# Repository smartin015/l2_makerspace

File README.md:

# Level 2 Makerspace

http://l2making.com/

## Overview

This repository contains design docs, software tools, work tracking, and other digital assets to support a Level 2 Makerspace.

See [docs/design.md](https://github.com/smartin015/l2_makerspace/blob/master/docs/design.md) for more detail on the overall mission and planning.

## History & Current State

This is a passion project which started in late 2019 as a chance to collect several technologies and skills which were fun to learn
and had the potential for really interesting applications in making.

Through 2020, my focus has been on prototyping and proving various concepts, including:

* Templates & basic protocols & frameworks (e.g. ROS2, ./infra/base messages & docker container processes)
* Integrations (e.g. Todoist for creating projects, Docker for launching sequences)
* Early hardware proofs of concept (simulation with Webots and publishing compressed point cloud data from Realsense D435 cameras)
* Visualization (particularly in VR, see ./infra/vr/client)
* Networking (e.g. routing between internal ROS network and external VR/app server)

## Roadmap

* See http://app.l2making.com/#project/TODO

## Support

This software is provided as-is with no guarantee of support. 

However, contributions are welcome - please reach out if you're interested
in helping with development.

### Lessons Learned

The following is a collection of details which were learned over hours of frustration. Please read through these if you're stuck on something, and
add new lessons learned.

* ROS2 uses DDS as a backing networking protocol - and it [has issues](https://answers.ros.org/question/296828/ros2-connectivity-across-docker-containers-via-host-driver/) when your run docker containers with the "host" network mode. For simplicity, always use `network_mode: bridge` when setting up docker nodes via docker-compose.
* Docker support for GPU acceleration is device-specific: http://wiki.ros.org/docker/Tutorials/Hardware%20Acceleration#Intel
* A ROS2 subscriber can receive a topic message only if its QOS profile is compatible with the QOS profile of the publisher - [src](https://answers.ros.org/question/304946/ros2-retrieving-qos-settings-for-a-topic/). Nothing tells you this; the messages just aren't received.
* The default docker "bridge" network doesn't allow lookups by container name, only by IP address - must use a user-defined container for name resolution
* ROS message transport (Fast RTPS) breaks if the same PID and IP address are used more than once (https://github.com/ros2/rmw_fastrtps/issues/349)
* If long-running nodes exit with error (137), it's an OOM. `docker ps -a` to find termination time, then `less /var/log/kern.log` and go to the time of death to correlate. 
* ROS nodes don't by default allow you to make nested async calls (e.g. publish from a subscriber callback). A `ReentrantCallbackGroup` must be used (see [vr node](https://github.com/smartin015/l2_makerspace/blob/master/infra/ros/vr/node.py) for an example that also supports service call deadlines).
* Webots ros integration requires the following environment variables to run (as well as sourcing the ROS setup.bash file):
  *  `export LD_LIBRARY_PATH="$LD_LIBRARY_PATH:$WEBOTS_HOME/lib/controller"`
  *  `export PYTHONPATH="$PYTHONPATH:$WEBOTS_HOME/lib/controller/python36"`
  *  `export WEBOTS_HOME=/usr/local/webots`
* As of 2020Q2, Webots doesn't export debian packages for ROS2 Eloquent. If using Crystal, the examples need to be modified to remove QoS settings on publisher definitions:
  *  `/opt/ros/crystal/lib/python3.6/site-packages/webots_ros2_examples/example_controller.py`
  *  `vim /opt/ros/crystal/lib/python3.6/site-packages/webots_ros2_core/webots_node.py`
* You can build webots from source for eloquent; this is probably easier.
* Webots ROS2 Node class has a timer that calls a `timer_callback` callback - accidentally overriding this causes the controller to halt. There's also naming collisions in rclp if you name something "Sequence"
* Sometimes docker-compose takes a looong time to start, with no console output. This was because there was low entropy on the server in order to open a secure connection (see [here](https://github.com/docker/compose/issues/6552))
* Streaming data from Webots requires setting IPC to "host" mode on the docker container; otherwise it exits with a "code 245"
* Ubuntu hides raspi install images for older versions (e.g. 18.04 LTS). You can find them [here](http://cdimage.ubuntu.com/releases/bionic/release/) - but raspbian is the most compatible for running e.g. D435 cameras.
* There's a *ton* of manual effort in setting up a realsense camera on raspi.
  * If you get frame drops, try updating the firmware on the camera. There's some "uvcvideo" kernel module patching stuff that didn't actually work, but could also be helpful. [details](https://eleccelerator.com/wiki/index.php?title=Raspbian_Buster_ROS_RealSense)
* Godot uses `scons` for development. You have to build the binary, then the export templates separately (see [here](https://docs.godotengine.org/en/3.0/development/compiling/compiling_for_x11.html) for linux binary, and [here](https://docs.godotengine.org/en/latest/development/compiling/compiling_for_android.html#building-the-export-templates) for android export templates)
* Super useful librealsense docs around camera intrinsics and projection: [link](https://github.com/IntelRealSense/librealsense/wiki/Projection-in-RealSense-SDK-2.0#intrinsic-camera-parameters)
  * Remember to build with android\_arch=armv7 or else the project will fail to export.
* Can generate space skyboxes with [link](http://wwwtyro.github.io/space-3d), but have to convert (see [link](https://www.reddit.com/r/godot/comments/baw27a/how_to_use_spacescape_skybox_in_godot/))
* Using the Godot OVR toolkit, 2D panels (i.e. most tools in L2 VR) are rendered with the viewport size matching the device resolution. This means tools can have different sizes if they're rendered on different devices (or if you resize the window). Setting display resolution to 2880x1600 makes them match.
* Along with executables, ros2 packages export "components" which can be composeable into nodes. this allows interprocess communciation and other goodies, but is hard to discover. `ros2 component types` (note: not `ros2 components list`) shows which components can be composed.
* Set `"insecure-registries":["<hostname>:5000"]` in /etc/docker/daemon.json and `sudo service docker restart` to allow non-https use of local registry

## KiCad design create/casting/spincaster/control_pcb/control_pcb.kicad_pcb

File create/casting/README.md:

# Casting and Smithing Automation

## Purpose

Automate the casting of metals/resins and "forging" of ductile materials.

## Ideas

TODO

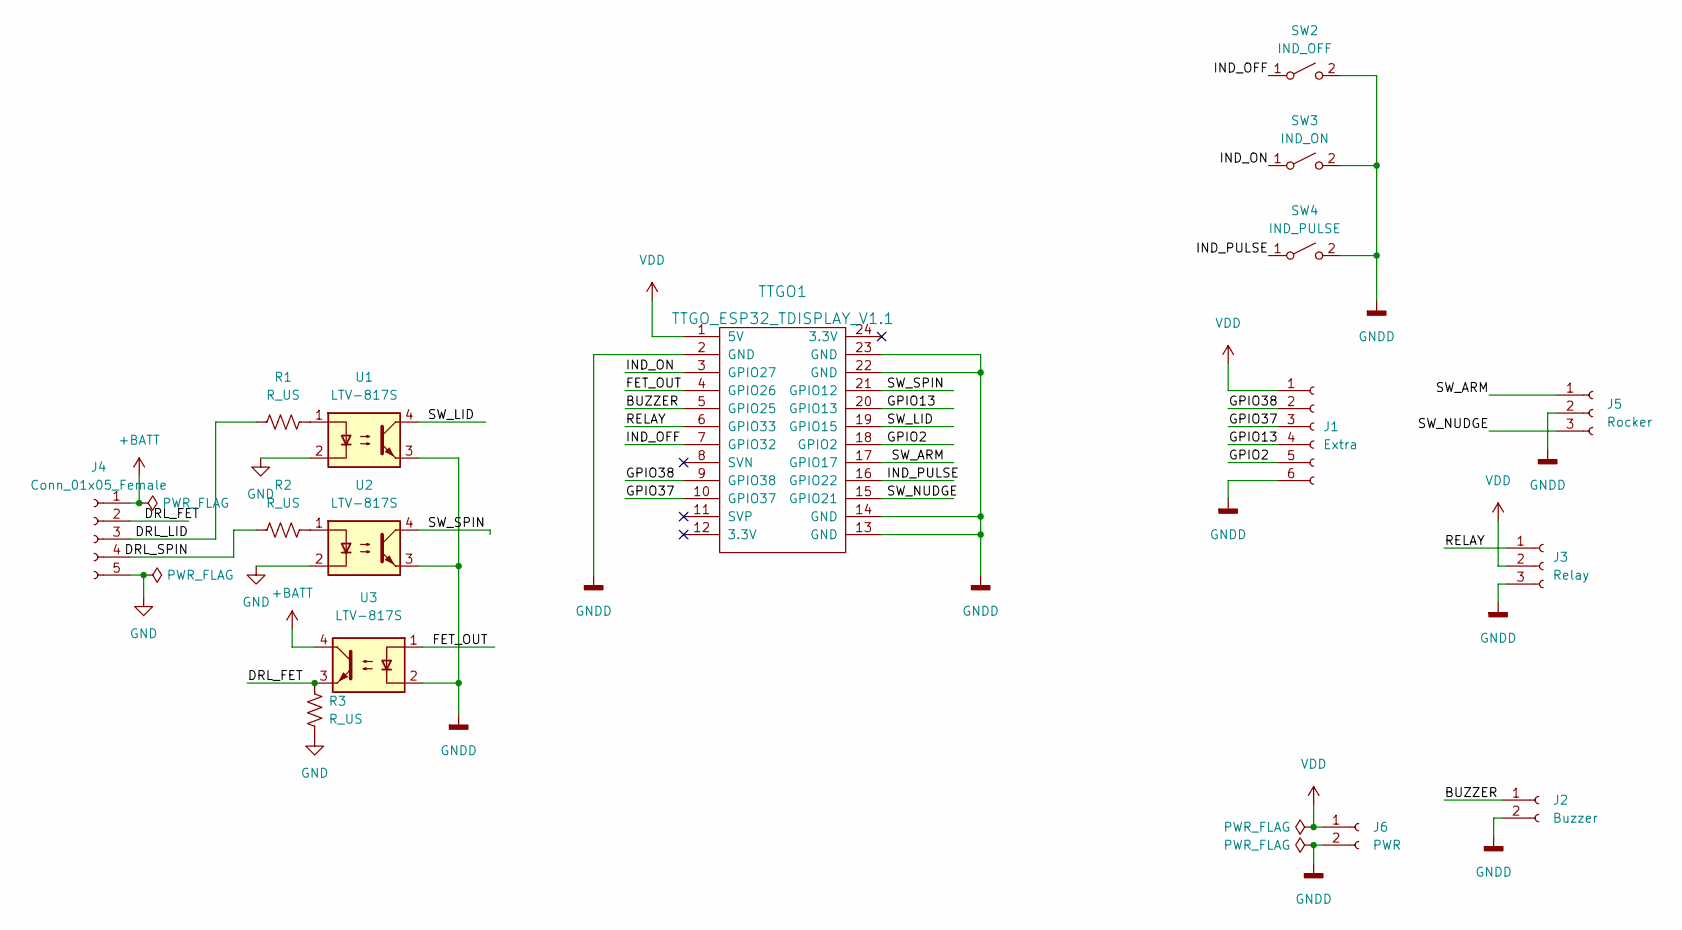
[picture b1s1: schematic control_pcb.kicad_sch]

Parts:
J1: Extra; PinHeader_1x06_P2.54mm_Vertical
J2: Buzzer; JST_PH_B2B-PH-K_1x02_P2.00mm_Vertical
J3: Relay; JST_PH_B3B-PH-K_1x03_P2.00mm_Vertical
J4: Conn_01x05_Female; Molex_KK-254_AE-6410-05A_1x05_P2.54mm_Vertical
J5: Rocker; JST_PH_B3B-PH-K_1x03_P2.00mm_Vertical
J6: PWR; JST_PH_B2B-PH-K_1x02_P2.00mm_Vertical
R1, R2, R3: R_US; R_0805_2012Metric
SW2: IND_OFF; SW_PUSH_6mm_H5mm
SW3: IND_ON; SW_PUSH_6mm_H5mm
SW4: IND_PULSE; SW_PUSH_6mm_H5mm
TTGO1: TTGO_ESP32_TDISPLAY_V1.1; TTGO_ESP32_TDisplay_v1.1
U1, U2, U3: LTV-817S; SMDIP-4_W9.53mm

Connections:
+BATT: J4.1, U3.4
/BUZZER: J2.1, TTGO1.5 (GPIO25)
/DRL_FET: J4.2, R3.1, U3.3
/DRL_LID: J4.3, R1.1
/DRL_SPIN: J4.4, R2.1
/FET_OUT: TTGO1.4 (GPIO26), U3.1
/GPIO2: J1.5, TTGO1.18 (GPIO2)
/GPIO13: J1.4, TTGO1.20 (GPIO13)
/GPIO37: J1.3, TTGO1.10 (GPIO37)
/GPIO38: J1.2, TTGO1.9 (GPIO38)
/IND_OFF: SW2.1 (A), TTGO1.7 (GPIO32)
/IND_ON: SW3.1 (A), TTGO1.3 (GPIO27)
/IND_PULSE: SW4.1 (A), TTGO1.16 (GPIO22)
/RELAY: J3.1, TTGO1.6 (GPIO33)
/SW_ARM: J5.1, TTGO1.17 (GPIO17)
/SW_LID: TTGO1.19 (GPIO15), U1.4
/SW_NUDGE: J5.3, TTGO1.15 (GPIO21)
/SW_SPIN: TTGO1.21 (GPIO12), U2.4
GND: J4.5, R3.2, U1.2, U2.2
GNDD: J1.6, J2.2, J3.3, J5.2, J6.2, SW2.2 (B), SW3.2 (B), SW4.2 (B), TTGO1.2 (GND), TTGO1.13 (GND), TTGO1.14 (GND), TTGO1.22 (GND), TTGO1.23 (GND), U1.3, U2.3, U3.2
unnamed: R1.2, U1.1
unnamed: R2.2, U2.1
VDD: J1.1, J3.2, J6.1, TTGO1.1 (5V)

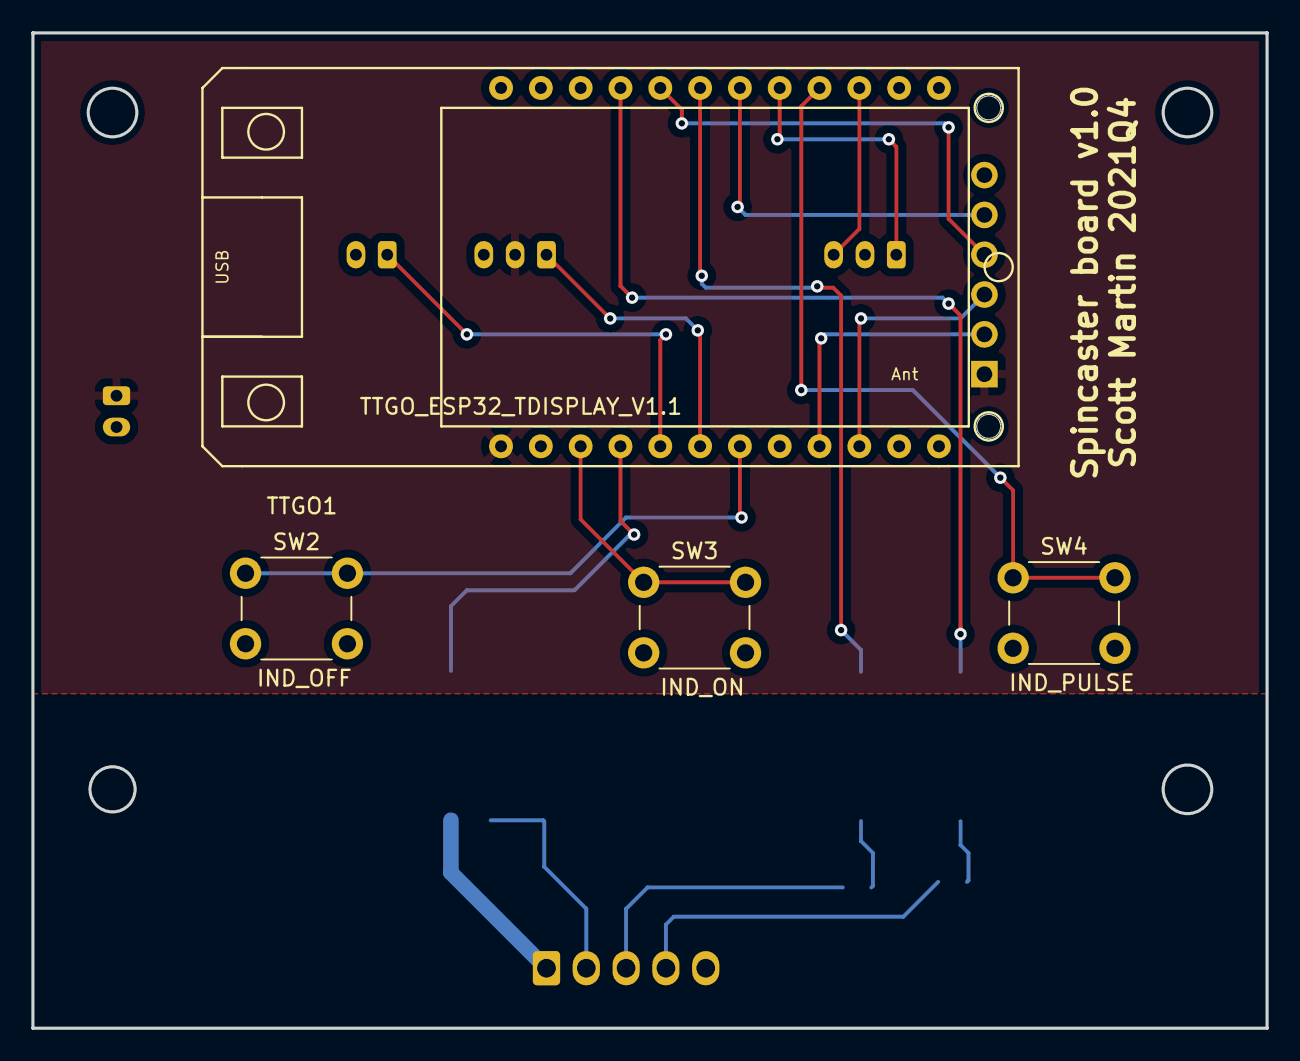
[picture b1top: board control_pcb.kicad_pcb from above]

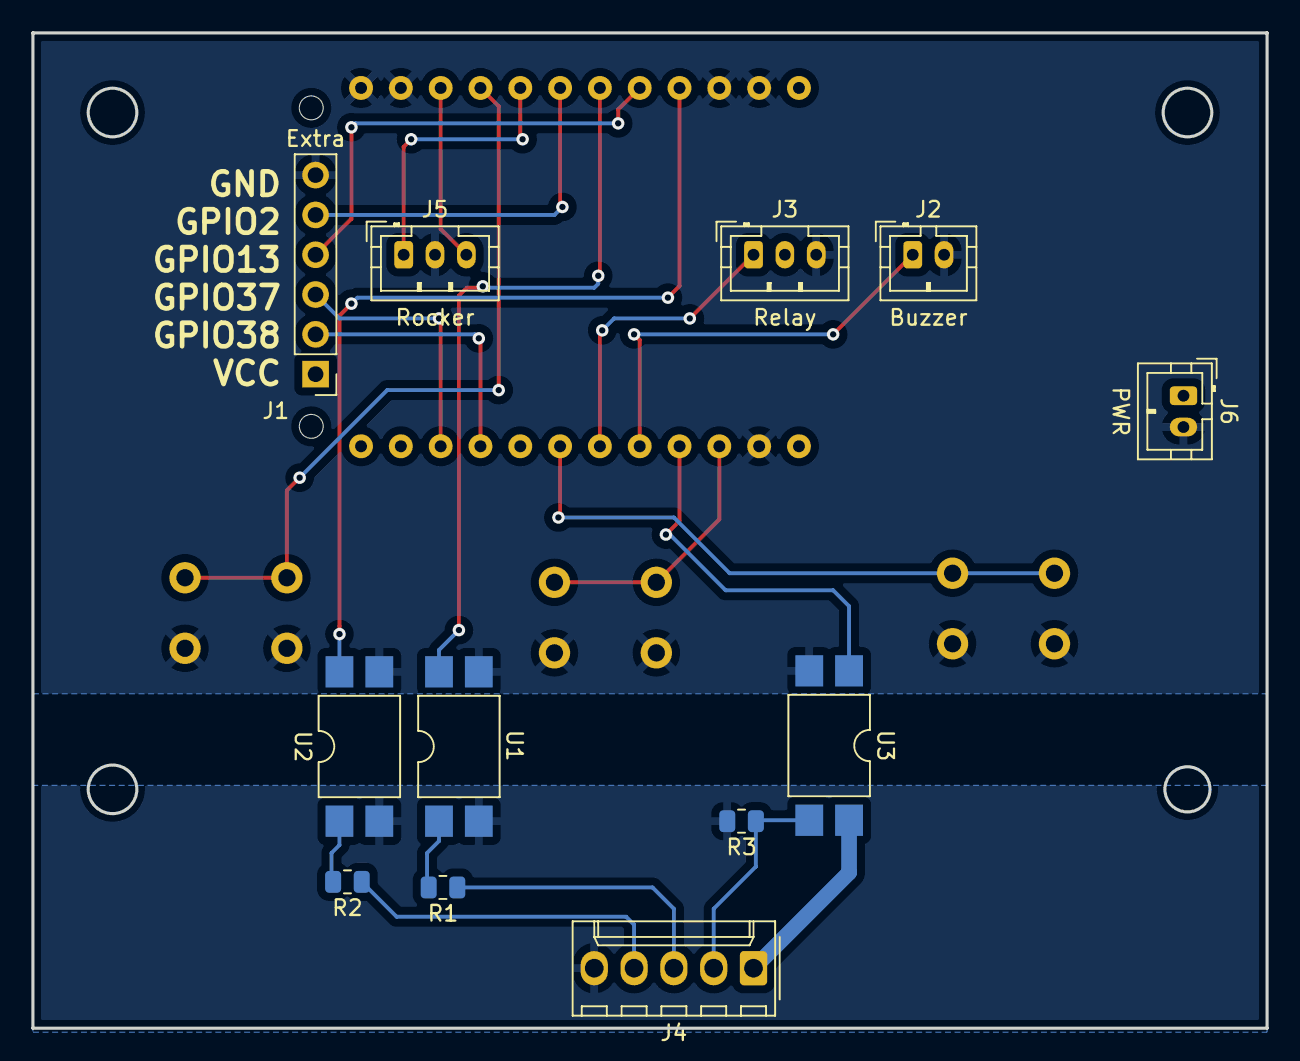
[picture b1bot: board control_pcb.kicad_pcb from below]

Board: 2 copper layers, 78.7 x 63.5 mm, 16 parts (12 on the bottom side), 23 nets.

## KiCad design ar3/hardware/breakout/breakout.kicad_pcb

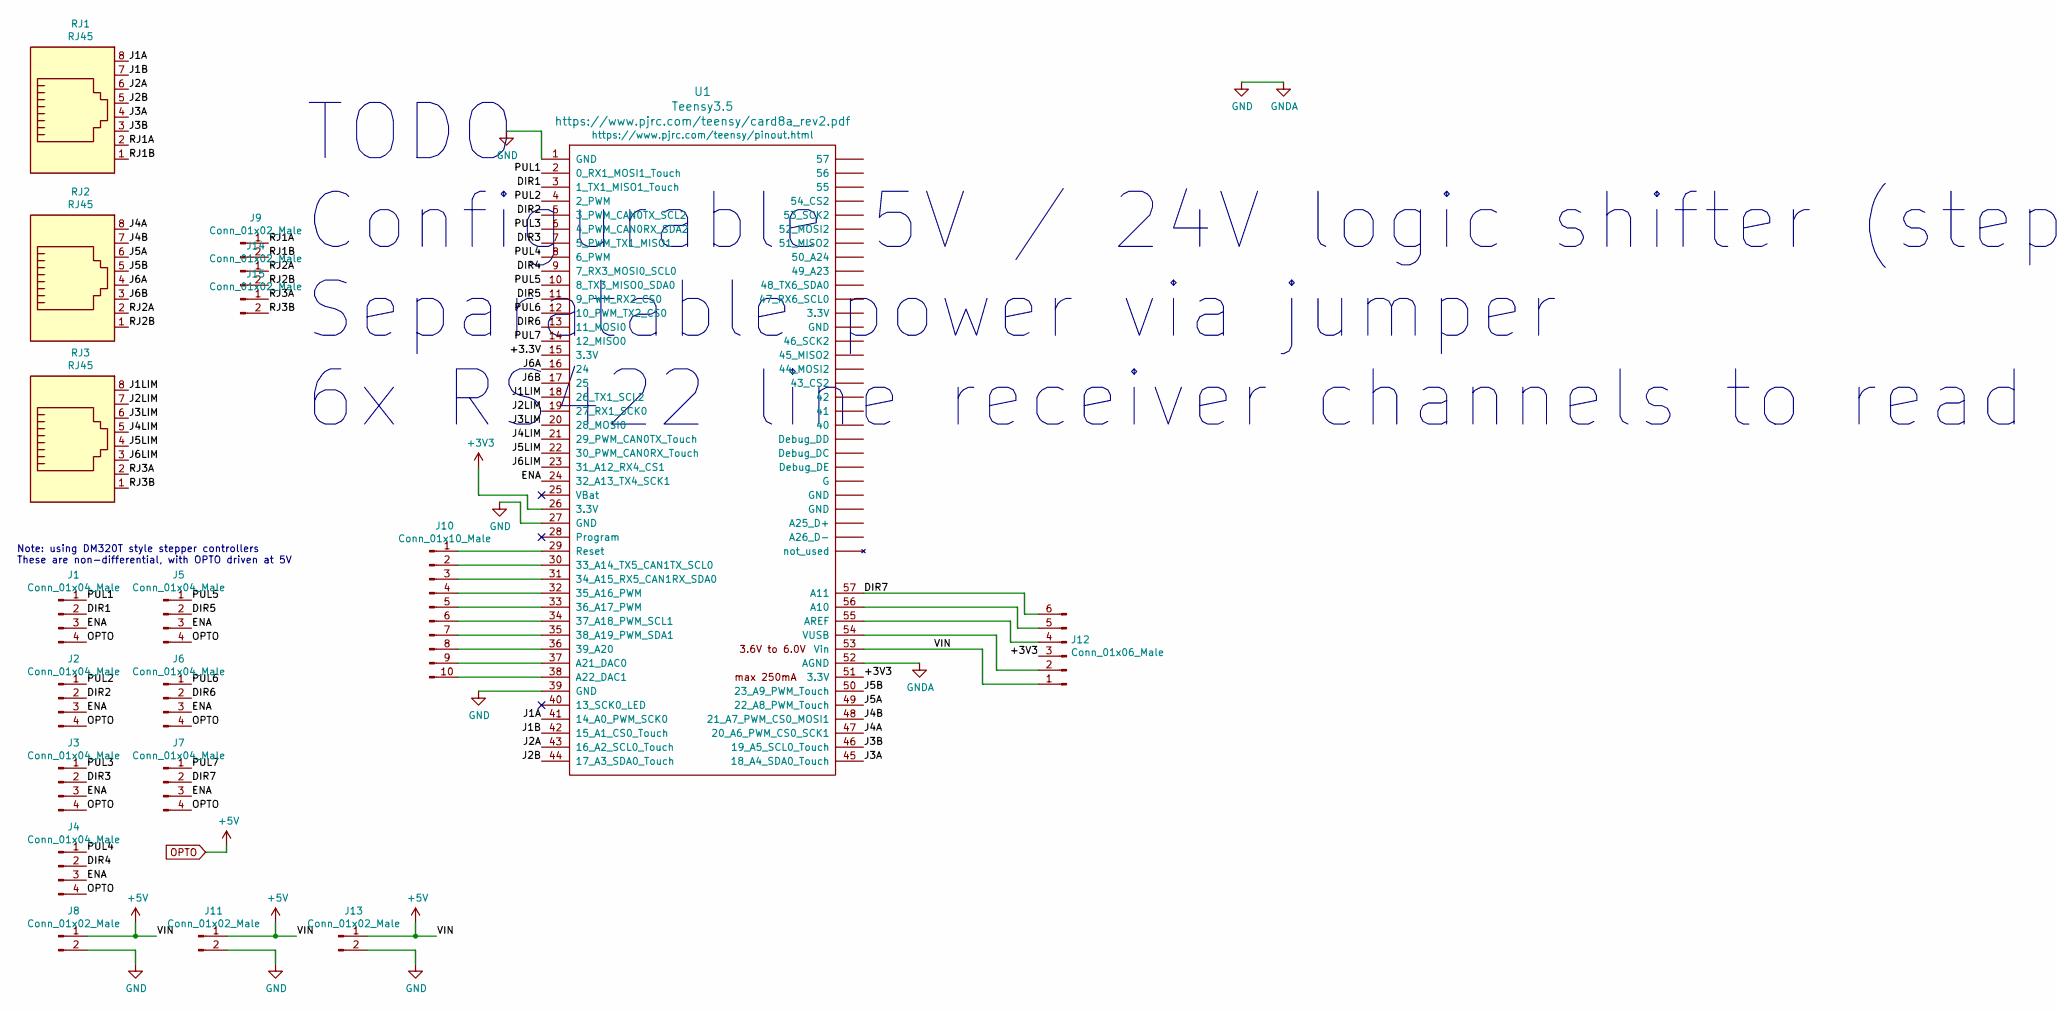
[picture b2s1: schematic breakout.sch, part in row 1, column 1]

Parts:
J1, J2, J3, J4, J5, J6, J7: Conn_01x04_Male; JST_PH_B4B-PH-K_1x04_P2.00mm_Vertical
J8, J9, J11, J13, J14, J15: Conn_01x02_Male; PinHeader_1x02_P2.54mm_Vertical
J10: Conn_01x10_Male; PinHeader_1x10_P2.54mm_Vertical
J12: Conn_01x06_Male; PinHeader_1x06_P2.54mm_Vertical
RJ1, RJ2, RJ3: RJ45; RJ45_Amphenol_54602-x08_Horizontal
U1: Teensy3.5; Teensy35_36

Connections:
+3V3: J12.3, U1.26 (3.3V), U1.51 (3.3V)
/DIR1: J1.2, U1.3 (1_TX1_MISO1_Touch)
/DIR2: J2.2, U1.5 (3_PWM_CAN0TX_SCL2)
/DIR3: J3.2, U1.7 (5_PWM_TX1_MISO1)
/DIR4: J4.2, U1.9 (7_RX3_MOSI0_SCL0)
/DIR5: J5.2, U1.11 (9_PWM_RX2_CS0)
/DIR6: J6.2, U1.13 (11_MOSI0)
/DIR7: J7.2, J12.6, U1.57 (A11)
/ENA: J1.3, J2.3, J3.3, J4.3, J5.3, J6.3, J7.3, U1.24 (32_A13_TX4_SCK1)
/J1A: RJ1.8, U1.41 (14_A0_PWM_SCK0)
/J1B: RJ1.7, U1.42 (15_A1_CS0_Touch)
/J1LIM: RJ3.8, U1.18 (26_TX1_SCL2)
/J2A: RJ1.6, U1.43 (16_A2_SCL0_Touch)
/J2B: RJ1.5, U1.44 (17_A3_SDA0_Touch)
/J2LIM: RJ3.7, U1.19 (27_RX1_SCK0)
/J3A: RJ1.4, U1.45 (18_A4_SDA0_Touch)
/J3B: RJ1.3, U1.46 (19_A5_SCL0_Touch)
/J3LIM: RJ3.6, U1.20 (28_MOSI0)
/J4A: RJ2.8, U1.47 (20_A6_PWM_CS0_SCK1)
/J4B: RJ2.7, U1.48 (21_A7_PWM_CS0_MOSI1)
/J4LIM: RJ3.5, U1.21 (29_PWM_CAN0TX_Touch)
/J5A: RJ2.6, U1.49 (22_A8_PWM_Touch)
/J5B: RJ2.5, U1.50 (23_A9_PWM_Touch)
/J5LIM: RJ3.4, U1.22 (30_PWM_CAN0RX_Touch)
/J6A: RJ2.4, U1.16 (24)
/J6B: RJ2.3, U1.17 (25)
/J6LIM: RJ3.3, U1.23 (31_A12_RX4_CS1)
/PUL1: J1.1, U1.2 (0_RX1_MOSI1_Touch)
/PUL2: J2.1, U1.4 (2_PWM)
/PUL3: J3.1, U1.6 (4_PWM_CAN0RX_SDA2)
/PUL4: J4.1, U1.8 (6_PWM)
/PUL5: J5.1, U1.10 (8_TX3_MISO0_SDA0)
/PUL6: J6.1, U1.12 (10_PWM_TX2_CS0)
/PUL7: J7.1, U1.14 (12_MISO0)
/RJ1A: J9.1, RJ1.2
/RJ1B: J9.2, RJ1.1
/RJ2A: J14.1, RJ2.2
/RJ2B: J14.2, RJ2.1
/RJ3A: J15.1, RJ3.2
/RJ3B: J15.2, RJ3.1
GND: J8.2, J11.2, J13.2, U1.1 (GND), U1.27 (GND), U1.39 (GND), U1.52 (AGND)
unnamed: J10.1, U1.29 (Reset)
unnamed: J10.2, U1.30 (33_A14_TX5_CAN1TX_SCL0)
unnamed: J10.3, U1.31 (34_A15_RX5_CAN1RX_SDA0)
unnamed: J10.4, U1.32 (35_A16_PWM)
unnamed: J10.5, U1.33 (36_A17_PWM)
unnamed: J10.6, U1.34 (37_A18_PWM_SCL1)
unnamed: J10.7, U1.35 (38_A19_PWM_SDA1)
unnamed: J10.8, U1.36 (39_A20)
unnamed: J10.9, U1.37 (A21_DAC0)
unnamed: J10.10, U1.38 (A22_DAC1)
unnamed: J12.2, U1.54 (VUSB)
unnamed: J12.4, U1.55 (AREF)
unnamed: J12.5, U1.56 (A10)
OPTO: J1.4, J2.4, J3.4, J4.4, J5.4, J6.4, J7.4, J8.1, J11.1, J12.1, J13.1, U1.53 (Vin)

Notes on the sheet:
Note: using DM320T style stepper controllers These are non-differential, with OPTO driven at 5V
TODO Configurable 5V / 24V logic shifter (stepper drivers) Separatable power via jumper 6x RS422 line receiver channels to read encoders w/ differential signal

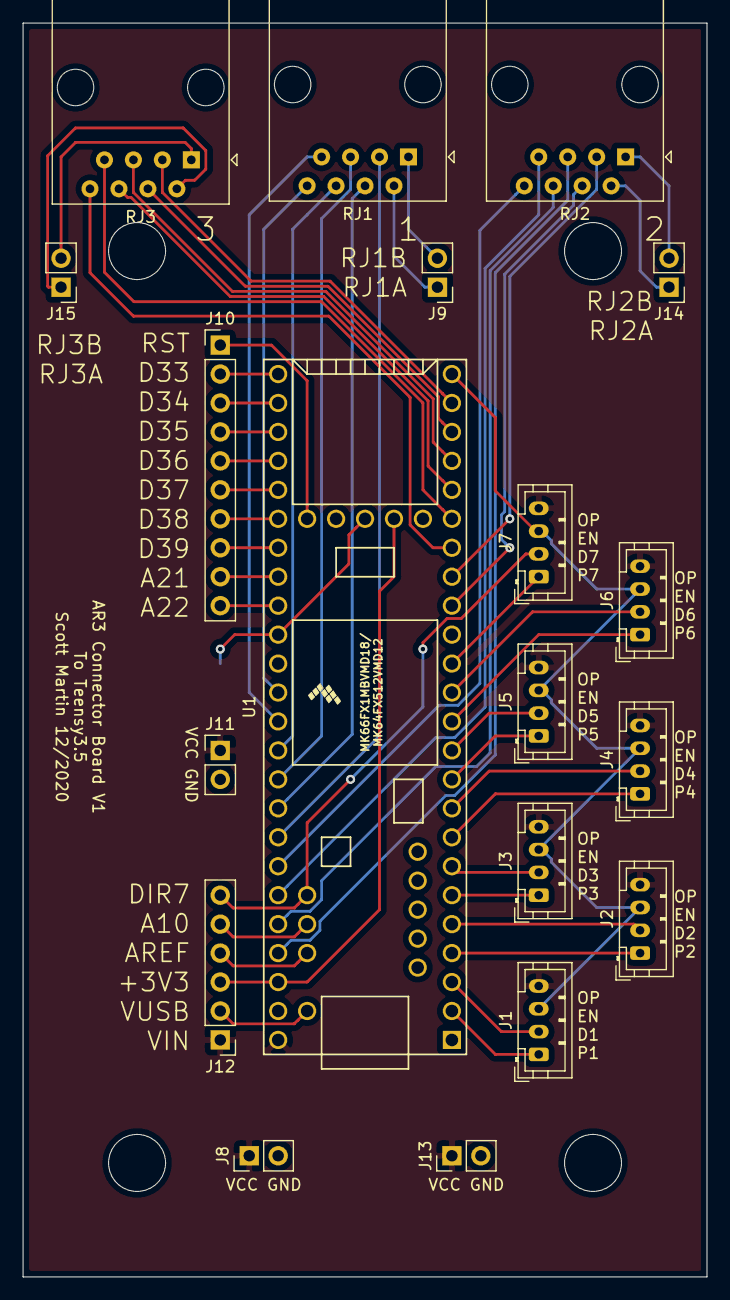
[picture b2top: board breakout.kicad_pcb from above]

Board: 2 copper layers, 60.0 x 110.0 mm, 19 parts (0 on the bottom side), 55 nets.

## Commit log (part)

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2019-12-31 add editor settings
2019-12-31 Add example icon images
2020-01-02 add sketchup file
2020-01-10 Add godot unit testing capability
2020-01-13 First working version of multiplayer, plus keyboard/mouse failover when not using VR
2020-01-13 Add example project message, make storage persist in a file and combine postgres db connection w/ ros2 node
2020-01-14 Moved readme -> docs/design.md, created new top level readme
2020-01-15 Add a starter "bootstrap" doc
2020-01-16 Added some side stuff, fixed cloud deploy & vr server
2020-01-16 Create infra folder and move stuff there
2020-01-16 rm docker.md
2020-01-16 Further refactoring / rearranging
2020-01-17 Added skeleton for todoist tasks ros node
2020-01-19 Add initial example chrome extension
2020-01-22 Continued development on RVL for godot
2020-01-24 Fixed ros talker/listener console flush problem
2020-01-24 Add crappy ros message to typescript interface generator
2020-01-24 Comment out debug text
2020-01-25 Comment out player echo code
2020-01-25 fix apk
2020-01-26 Fixed keyboard navigation and mouselook
2020-01-26 Allowed making cubes with 'g' keyboard press, networked and persistent
2020-01-28 Moved client/server VR folders out of projects, cleaned up init logic in clint
2020-01-29 Added super basic example of poly mesh loading
2020-01-30 Clean up objparse code, unit test cube and plane meshes
2020-01-30 Make mesh parser resilient to missing texture/normal map
2020-01-31 Checkpoint; refactor docs and streamline (read: break) all the ros nodes
2020-02-04 Started using OQ toolkit, built working ros todoist publisher, denormalized rvl code into ros/depth_camera, started ros CAD node
2020-02-07 added notes on system dashboard (infra/ros/dashboard/README.md)
2020-02-07 Working example of webapp talking with ros bridge in server mode
2020-02-07 Improve puppetplayer aesthetic (use oculus controllers)
2020-02-09 Added VR HUD to left controller, plus control zone logic
2020-02-13 Updated server & vr client
2020-03-04 Optimistic commit
2020-03-22 Got ros bridge working with ros services, added AddTwoInts test service to godot, and fixed PushObject3D
2020-03-23 Actually add the srv files
2020-03-25 Fix up VR server message publishers
2020-03-28 Set up gazebo with ROS2 eloquent, default world that exports model_state
2020-03-28 Fix up vr server
2020-03-28 VR differ node created; does nothing, but does it well
2020-03-29 Add (tested) logic to fetch object3d from postgres; logic (untested) to resolve diffs between gazebo & VR
2020-04-02 Now working: sync from gazebo+postgres to VR server, with timeouts and async handling
2020-04-02 Migrate SDF, ROS files to folders to match server
2020-04-05 Fix SDF object removal
2020-04-13 VR joints now update when receiving a published ROS message via ros2-web-bridge
2020-04-14 Added dummy supervisor node for starting docker containers from ROS
2020-04-18 Add supervisor test dir
2020-04-18 Added vr server unsubscribe, docker-compose settings for webots+controller
2020-04-18 Hooked up file watch to postgres DB update
2020-04-19 Got ros-initialized webots simulator working
2020-04-20 Got server publishing joint state from webots
2020-04-20 Created sample rangefinder via extern controller
2020-04-23 Add blank image to rangefinder
2020-04-23 Added single webots world demoing pendant, single motor, and rangefinder
2020-04-24 Moved l2 gdscripts tacked on after Actor creation into actor/ folder; got Base64 encoded point clouds over websockets working with DepthRender. Still need to overcome the frame size limit though
2020-04-25 Fixed Lock msg publish in VR server, tweaks to demo.wbt
2020-04-25 Fix cone & transparency construction in parse/proto, also fix up pendant and control zone construction & behavior
2020-04-26 Set up godot for APK export and add raw UDP subscription in ROSBridge
2020-05-03 More work on sequence UI
2020-05-04 Added networked canvas/whiteboard, plus development on bootstrap script and sequence GraphEdit
2020-05-06 Cleaned up logging and started using infra/base/bootstrap/local.sh
2020-05-06 More tweaks to bootstrapping
2020-05-10 Messed with VR environment, also added trailing console panel from ROS string topic
2020-05-10 Add basic overview of how docker build system works in docker.md
2020-05-23 Fix rvl gdscript, break tests into rvl and vle
2020-05-23 Tweaked gdscript->python converter and verified rvl.py works
2020-05-23 More tweaks to rvl encode/decoe
2020-05-23 Fix depth render to properly display depth camera image
2020-05-23 Implement dewarp/deproject for DepthRender
2020-05-25 Add continuous floor navigation, fixed multiplayer desync on canvas
2020-05-28 Added workspace switching controls, plus server-side state for all tools
2020-06-07 Added drawing of different shapes to canvas
2020-06-12 Reorganize files, delete cruft, implement world-positioned player menu
2020-06-13 Added workspace creation and editing local to VR
2020-06-14 Small fixes to new tool spawning, workspace selecting/switching, and selectable show/hide toggle
2020-06-14 Reorganized selectable, added workspace movement of tools
2020-06-18 Update ros bridge version
2020-06-18 Remove pid:host hack as bug is now closed - https://github.com/ros2/rmw_fastrtps/issues/349
2020-07-14 added newest OQ toolkit, also set up saveable user config, configurable workshop rooms, and (untested) enable/disable of dangerful VR controls
2020-07-16 Added sshfs mount script, plus debug pane. Set menu enable/disable to V gesture
2020-07-17 Plumbing for snapshotting & loading workspace snapshots
2020-07-21 Update virtual desktop example, prep for automatic client
2020-07-24 Derped with webots startup script, added 3DTransformer widget skeleton for new object movement UI
2020-07-26 Add gstreamer_texture thing; currently not working because cant load gstreamer playbin element
2020-07-26 First actual evidence any of this gstreamer crapola works
2020-07-27 Moved pipeline var to external param
2020-07-27 Changed texture init, got test video (sort of) working
2020-08-06 Updated L2 workshop obj file, solved gstreamer video alignment issues
2020-08-07 A bunch of half-baked changes
2020-08-10 Added ros state (topics, services, nodes) synchronization to VR servier, shows up in console list
2020-08-11 Cleanup, fixed run_local.sh, fixed app build/deploy, fixed VR deploy from docker-compose
2020-08-12 Successful publish from supervisor node
2020-08-14 Moved volumes to common volumes/ directory so run_local.sh can load correctly from paths
2020-08-15 Successfully published parameterized sequence node from VR
2020-08-16 Todoist: extract tasks matching `l2 sometask` and queue them up for supervisor
2020-08-18 Made app server a ros node (for better syncing) and improved run_local.sh behavior
2020-08-21 Schema generation partially works... still lots of bugs. this commit doesnt actually work
2020-09-24 Added active project selection from l2app
2020-10-01 Merged some changes
2020-11-13 Added readme on RVL deps
2020-11-15 Working example of variable length encoding with CUDA (45ms per full frame vs 0.5s with CPU)
2020-11-16 RVL on cuda now complete - image decodes partially, but it looks like encoder is not actually reading the write image segments
2020-12-01 Remove dbg and expensive np commands from CUDA RVL
2020-12-03 Added ar3 kicad basic stuff
2020-12-04 Partial fix to allow gpu decoding of RVL
2020-12-06 Successfully GPU-decoded RVL into deprojected point cloud and visualized in matplotlib
2020-12-07 Converting docker file into l2 docker container for ros capability, added UDP send/receive examples
2020-12-07 Add base firmware files
2020-12-07 Got robot working with simple webots controller
2020-12-10 Added v1 gerber files for AR3 controller PCB, plus simple arduino encoder code
2020-12-13 ar3 node now dances in webots
2020-12-18 Publish joint_state for ar3 webots sim
2020-12-23 First semi-working version of moveit_servo using new configs
2020-12-24 Some additional work on moveit config, but mostly attempting a refactor of AR3 robotic arm firmware
2020-12-26 Performant send RVL cuda code, broke out kernel config logic
2020-12-27 Added new firmware for AR3 LCD display
2020-12-27 Change ar3 status screen layout
2020-12-29 Added push/pull to local registry
2020-12-30 Finally got flatbuffers, websockets working in native mode (probably broke esp32 mode)
2020-12-31 added module
2021-01-02 Speculative ino for testing encoders on AR3
2021-01-03 Added motor limits, updated ar3 node to use scaled targets
2021-01-05 Add hacky pca code
2021-01-08 Updated encoder qual on AR3
2021-01-10 More speculative work on AR3 firmware simulation
2021-01-11 More work on virtual AR3 firmware for webots; got expected step target telemetry out of binary and into python receiver via ZMQ
2021-01-13 Added TODOs to AR3 breakout schematic
2021-03-11 add old build script
2021-03-12 Got AR3 sim up and running again with non-webots selectable sim
2021-03-13 Partial refactor of depth camera, probably not all working
2021-04-03 Partial commit of refactor to ar3 code
2021-04-04 Added timeseries graph to ar3 web display, made some bugfixes in velocity control loop
2021-04-14 Added AR3 log
2021-04-16 Got teensy version of ar3 firmware to build
2021-04-16 Added limit override button to arm GUI
2021-04-20 Firmware now has adjustable number of joints and simpler behavior WRT directions (less config). AR3 native client now accepts -j as parameter for number of joints and exposes to the web interface. St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
2021-04-23 Fix small bugs in sock2ser python script for driving the trashbot
2021-04-28 Updated ar3 firmware to allow for 3-axis robot positioning
2021-04-30 Added control favicon
2021-05-02 Start adding microcontroller timer code
2021-05-04 Switched to PID velocity tuning, also now reporting back telementry on each motion::update for better resolution
2021-05-06 Correct assignment bug in PID tuning for tribot firmware, also open loop step tracking
2021-05-10 AR3 firmware: added ability to dynamically set settings values for PID, max speed/accel etc
2021-05-25 Optimistic commit of firmware edits for async timer based simulation of firmware loop
2021-05-25 Updated native thread based firmware in AR3 to have better performance
2021-05-27 AR3 firmware bugfixes - mostly related to endianness. Also added target bubbles in polar chart
2021-05-28 Small cleanup to ar3/control/
2021-05-28 renamed native_client.py to broker.py
2021-06-02 Got AR3 firmware working on tribot with PID loop, smoothly
2021-06-04 Added reconnect to webcam on timelapse capture.py
2021-06-18 Added standby page (not yet hooked up) and variations on touchmark
2021-06-22 partial progress
2021-07-03 Optimistic commit, lathe_5axis
2021-09-28 Added vacuum mixer cadquery files
2021-11-15 update gstreamer readme
2021-11-22 Added skeleton of network AV mqtt control
2021-11-23 network_av C++ impl now startable/stoppable via mqtt. still no web server though.
2021-11-30 Further updates to network_av - now has command line args, MQTT status output
2021-11-30 Optimistic commit - lots of refactors and such
2021-12-01 capture_urllib now capture_hls, passive scraping of all feeds. Also some small behavioral tweaks to network_av - no longer attempts to start an already running pipeline
2021-12-01 Merge, plus set realsense serial number
2021-12-01 Added run.sh to allow single-command start of HLS/MQTT streamer plus HTTP server
2021-12-02 Added mqtt to capture_hls
2021-12-03 Added raspberry pi camera configuration option for network_av
2021-12-31 Finished control PCB for fab
